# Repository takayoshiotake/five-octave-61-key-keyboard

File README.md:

# Five Octave

[![CC BY-SA 4.0][cc-by-sa-shield]][cc-by-sa]

A 61-key (5-octave) keyboard. Powered by [Vial](https://get.vial.today/) firmware.

## Layout

**Layer 0**:

📄 [keyboard-layout.png](layout/keyboard-layout.png) (v0.3.0)

MEMO: When pressed individually and released, it becomes the lower right keys (英数 and かな).

**Layer 1**:

📄 [keyboard-layout-1.png](layout/keyboard-layout-1.png)

**Layer 2**:

📄 [keyboard-layout-2.png](layout/keyboard-layout-2.png)

MEMO: I couldn't figure out how to achieve 'fn' with adafruit_hid, so I'm using Karabiner to remap right_option to 'fn' and using it that way.

**RAW data for Keyboard Layout Editor v0.15:**

📄 [keyboard-layout.rawdata.json](layout/keyboard-layout.rawdata.json)

```json
[{"a":4,"f":3},"Esc","!\n1","@\n2","#\n3","$\n4","%\n5","^\n6","&\n7","*\n8","(\n9",")\n0","_\n-","+\n=","|\n\\","~\n`"],
[{"w":1.5},"Tab","Q","W","E","R","T","Y","U","I","O","P","{\n[","}\n]",{"w":1.5},"BS"],
[{"w":1.75},"MO(1)\n\n\n英数","A","S","D","F","G","H","J","K","L",":\n;","\"\n'",{"w":2.25},"Return"],
[{"w":2.25},"Shift","Z","X","C","V","B","N","M","<\n,",">\n.","?\n/",{"w":1.75},"Shift","MO(2)"],
[{"w":1.25},"Ctrl",{"w":1.25},"Opt",{"w":1.25},"Cmd\n\n\n英数",{"a":7,"w":6.25},"6.25u",{"a":4},"Cmd\n\n\nかな","Opt"]
```

📄 [keyboard-layout-1.rawdata.json](layout/keyboard-layout-1.rawdata.json)

```json
[{"a":4,"f":3},"Esc",{"c":"#aaccaa"},"F1","F2","F3","F4","F5","F6","F7","F8","F9","F10","F11","F12",{"c":"#cccccc"},"|\n\\","~\n`"],
[{"w":1.5},"Tab",{"c":"#aaccaa"},"Home","Up","End","PgUp",{"c":"#cccccc"},"T","Y","BS",{"c":"#cccccc"},"I","O","P","{\n[","}\n]",{"w":1.5},"BS"],
[{"c":"#aaccaa","w":1.75},"","Left","Down","Right","PgDn",{"c":"#cccccc"},"G",{"c":"#aaccaa"},"Enter","kana",{"c":"#cccccc"},"K","L",":\n;","\"\n'",{"w":2.25},"Return"],
[{"w":2.25},"Shift","Z","X","C","V","B","N","M","<\n,",">\n.","?\n/",{"w":1.75},"Shift",{"c":"#aaccaa"},"",{"c":"#cccccc"}],
[{"w":1.25},"Ctrl",{"w":1.25},"Opt",{"w":1.25},"Cmd\n\n\n英数",{"a":7,"w":6.25},"6.25u",{"a":4},"Cmd\n\n\nかな","Opt"]
```

📄 [keyboard-layout-2.rawdata.json](layout/keyboard-layout-2.rawdata.json)

```json
[{"a":4,"f":3},"Esc",{"c":"#aaccaa"},"F1","F2","F3","F4","F5","F6","F7","F8","F9","F10","F11","F12",{"c":"#cccccc"},"|\n\\","~\n`"],
[{"w":1.5},"Tab","Q","W","E","R","T","Y","U","I","O","P",{"c":"#aaccaa"},"Up",{"c":"#cccccc"},"}\n]",{"w":1.5},"BS"],
[{"c":"#aaccaa","w":1.75},"CapsLock",{"c":"#cccccc"},"A","S","D","F","G","H","J","K","L",{"c":"#aaccaa"},"left","right",{"c":"#cccccc","w":2.25},"Return"],
[{"w":2.25},"Shift","Z","X","C","V","B","N","M","<\n,",">\n.",{"c":"#aaccaa"},"Down",{"c":"#cccccc","w":1.75},"Shift",{"c":"#aaccaa"},"",{"c":"#cccccc"}],
[{"w":1.25},"Ctrl",{"w":1.25},"Opt",{"w":1.25},"Cmd\n\n\n英数",{"a":7,"w":6.25},"6.25u",{"a":4},"Cmd\n\n\nかな","Opt"]]
```

- 🔗 [Keyboard Layout Editor](http://www.keyboard-layout-editor.com/)

## BOM

| Material | QTY | Note |
|-|-:|-|
| Five Octave MCU Board | 1 | |
| Five Octave Keys Board | 1 | |
| Five Octave Enclosure | 1 | |
| 0151660169 | 1 | Molex 0.50mm pitch FFC, Type A, 127.00mm, 16 circuits |

- 🔗 [Molex Connector Part Number - 15166-0169 | Molex](https://www.molex.com/en-us/products/part-detail/151660169)

### Five Octave MCU Board

| Material | Symbol | QTY | Note | JLCPCB Part # |
|-|-|-:|-|-|
| 30pF 0402 | C1, C2 | 2 | | [C1570](https://jlcpcb.com/partdetail/1922-0402CG300J500NT/C1570) |
| 1uF 0402 | C3, C4 | 2 | | [C52923](https://jlcpcb.com/partdetail/53938-CL05A105KA5NQNC/C52923) |
| 100nF 0402 | C5-C14 | 10 | | [C307331](https://jlcpcb.com/partdetail/291005-CL05B104KB54PNC/C307331) |
| 10uF 0402 | C15, C16 | 2 | | [C15525](https://jlcpcb.com/partdetail/16204-CL05A106MQ5NUNC/C15525) |
| HRO_TYPE-C-31-M-12 | J1 | 1 | USB Type-C Connector, Korean Hroparts Elec | [C165948](https://jlcpcb.com/partdetail/Korean_HropartsElec-TYPE_C_31_M12/C165948) |
| AFC01-S16FCC-00 | J2 | 1 | FFC Connector 0.50mm pitch 16 circuits, JUSHUO | [C262272](https://jlcpcb.com/partdetail/Jushuo-AFC01_S16FCC00/C262272) |
| WS2812C-2020-V1 | LED1 | 1 | NeoPixel RGB LED 2x2mm, Worldsemi | [C2976072](https://jlcpcb.com/partdetail/Worldsemi-WS2812C_2020V1/C2976072) |
| 10KΩ 0402 | R1, R3 | 2 | | [C25744](https://jlcpcb.com/partdetail/26487-0402WGF1002TCE/C25744) |
| 1KΩ 0402 | R2, R4 | 2 | | [C11702](https://jlcpcb.com/partdetail/12256-0402WGF1001TCE/C11702) |
| 27Ω 0402 | R5, R6 | 2 | | [C352446](https://jlcpcb.com/partdetail/Resi-AECR0402F27R0K9/C352446) |
| 5.1KΩ 0402 | R7, R8 | 2 | | [C25905](https://jlcpcb.com/partdetail/26648-0402WGF5101TCE/C25905) |
| SKRPANE010 | SW1, SW2 | 2 | Tactile Switch, ALPS ALPINE | [C470426](https://jlcpcb.com/partdetail/Alpsalpine-SKRPANE010/C470426) |
| RP2040 | U1 | 1 | MCU, Raspberry Pi | [C2040](https://jlcpcb.com/partdetail/RaspberryPi-RP2040/C2040) |
| W25Q64JVXGIQ | U2 | 1 | 64M-bit Serial Flash, Winbond Electronics | [C2940195](https://jlcpcb.com/partdetail/WinbondElec-W25Q64JVXGIQ/C2940195) |
| AP2112K-3.3TRG1 | U3 | 1 | 3.3V Linear Voltage Regulators | [C51118](https://jlcpcb.com/partdetail/DiodesIncorporated-AP2112K_33TRG1/C51118) |
| X322512MSB4SI | Y1 | 1 | 12MHz 20pF Crystal Resonator, SMD-3225, Yangxing Tech | [C9002](https://jlcpcb.com/partdetail/YangxingTech-X322512MSB4SI/C9002) | 

### Five Octave Keys Board

| Material | Symbol | QTY | Note | JLCPCB Part # |
|-|-|-:|-|-|
| 1N4148WS | D1-D61 | 61 | | [C2128](https://jlcpcb.com/partdetail/2485-1N4148WS/C2128) |
| CPG151101S11-16 | SW1-SW61 | 61 | How Swap Socket, Kailh | [C5156480](https://jlcpcb.com/partdetail/Kailh-CPG151101S1116/C5156480) | 
| AFC01-S16FCC-00 | J1 | 1 | FFC Connector 0.50mm pitch 16 circuits, JUSHUO | [C262272](https://jlcpcb.com/partdetail/Jushuo-AFC01_S16FCC00/C262272) |

- 🔗 [JLCPCB | Assembly Parts Lib](https://jlcpcb.com/parts)

### Five Octave Enclosure

| Material | Symbol | QTY | Note |
|-|-|-:|-|
| Five Octave Enclosure - Case || 1 | (or Enclosure v2) |
| Five Octave Enclosure - Top Frame || 1 | (or Enclosure v2) |
| Screw M2 x 8mm || 4 | Secure Case and Top Frame |
| Screw M2 x 5mm or 4mm || 4 | Secure Case and Five Octave MCU |
| Poron 1.5t 3mm x 120mm || 2 | For gasket mounting |
| Poron 1.5t 3mm x 60mm || 6 | For gasket mounting |
| Poron 1.5t 3mm x 40mm || 2 | For gasket mounting |

## Schematic and PCB

### Five Octave MCU

📄 [Five_Octave_MCU.kicad_sch](electronics/Five_Octave_MCU/Five_Octave_MCU.kicad_sch) (v1.0.0)

📄 [Five_Octave_MCU.kicad_pcb](electronics/Five_Octave_MCU/Five_Octave_MCU.kicad_pcb) (v1.0.0)

📄 [Five_Octave_MCU.svg](electronics/Five_Octave_MCU/Five_Octave_MCU.svg)

### Five Octave Keys

📄 [Five_Octave_Keys.kicad_sch](electronics/Five_Octave_Keys/Five_Octave_Keys.kicad_sch) (v1.0.0)

📄 [Five_Octave_Keys.kicad_pcb](electronics/Five_Octave_Keys/Five_Octave_Keys.kicad_pcb) (v1.0.0)

📄 [Five_Octave_Keys.svg](electronics/Five_Octave_Keys/Five_Octave_Keys.svg)

#### Key-matrix (8x8)

|    | C0    | C1   | C2  | C3  | C4    | C5    | C6     | C7    |
|----|-------|------|-----|-----|-------|-------|--------|-------|
| R0 | Esc   |      | 1   | 2   | 3     | 4     | 5      | 6     |
| R1 | Tab   |      |     | Q   | W     | E     | R      | T     |
| R2 | Caps  | Z    | X   | A   | S     | D     | F      | G     | 
| R3 | Shift | Ctrl | Opt | Cmd | Space | C     | V      | B     |
| R4 | 7     | 8    | 9   | 0   | -     | =     | \      | `     |
| R5 | Y     | U    | I   | O   | P     | [     | ]      | BS    |
| R6 | H     | J    | K   | L   | ;     | '     | Return | Fn    |
| R7 | N     | M    | ,   | .   | /     | Shift | Cmd    | MO(1) | 

## Mechanics

### Five Octave Enclosure

📄 [Five_Octave_Enclosure.FCStd](mechanics/Five_Octave_Enclosure.FCStd) (v1.0.1)

### Five Octave Enclosure v2

📄 [Five_Octave_Enclosure_v2.FCStd](mechanics/Five_Octave_Enclosure_v2.FCStd) (v2.1.2)

### Plate

📄 [Five_Octave_Plate.kicad_pcb](electronics/Five_Octave_Plate/Five_Octave_Plate.kicad_pcb) (v1.0.0)

## Firmware

You can use Vial or CircuitPython.

### Vial

- Built UF2
    - 📄 [takayoshiotake_five_octave_vial_20240103.uf2](vial-bin/takayoshiotake_five_octave_vial_20240103.uf2)
- Code
    -  🔗 <https://github.com/vial-kb/vial-qmk/tree/vial/keyboards/takayoshiotake/five_octave>
    -  🔗 <https://github.com/vial-kb/vial-qmk/tree/49f5eec0d46f3524850885ffae9dee2982312e50>

See [vial-porting](vial-porting) for more details.

### CircuitPython

Software for the Five Octave runs on CircuitPython.
Its CircuitPython is the same as the one for Octave (<https://github.com/takayoshiotake/octave-12-key-macropad>).

- Built UF2
    - 🔗 <https://adafruit-circuit-python.s3.amazonaws.com/index.html?prefix=bin/takayoshiotake_octave_rp2040/>
    - 📄 [adafruit-circuitpython-takayoshiotake_octave_rp2040-en_US-8.2.6.uf2](circuitpython-bin/adafruit-circuitpython-takayoshiotake_octave_rp2040-en_US-8.2.6.uf2)
- Code
    - 🔗 [adafruit/circuitpython](https://github.com/adafruit/circuitpython)
        - 🔗 <https://github.com/adafruit/circuitpython/tree/main/ports/raspberrypi/boards/takayoshiotake_octave_rp2040>

See [circuitpython-app/README.md](software/README.md) for application software.

## Gallery

Keycap: Drop + biip MT3 Extended 2048

MEMO: Alminum 6061 CNC + Bead blasting 120 mesh + Anodizing natural matte by JLCPCB (Five Octave Enclosure v1.0.0)

### Photos with Enclosure v2

Keycap: Drop + biip MT3 Extended 2048

MEMO: Alminum 6061 CNC + Bead blasting 150 mesh + Hardcoat anodizing natural matte by JLCPCB (Five Octave Enclosure v2.1.1)

## License

This work is licensed under a
[Creative Commons Attribution-ShareAlike 4.0 International License][cc-by-sa].

[![CC BY-SA 4.0][cc-by-sa-image]][cc-by-sa]

[cc-by-sa]: http://creativecommons.org/licenses/by-sa/4.0/
[cc-by-sa-image]: https://licensebuttons.net/l/by-sa/4.0/88x31.png
[cc-by-sa-shield]: https://img.shields.io/badge/license-CC%20BY--SA%204.0-lightgrey.svg

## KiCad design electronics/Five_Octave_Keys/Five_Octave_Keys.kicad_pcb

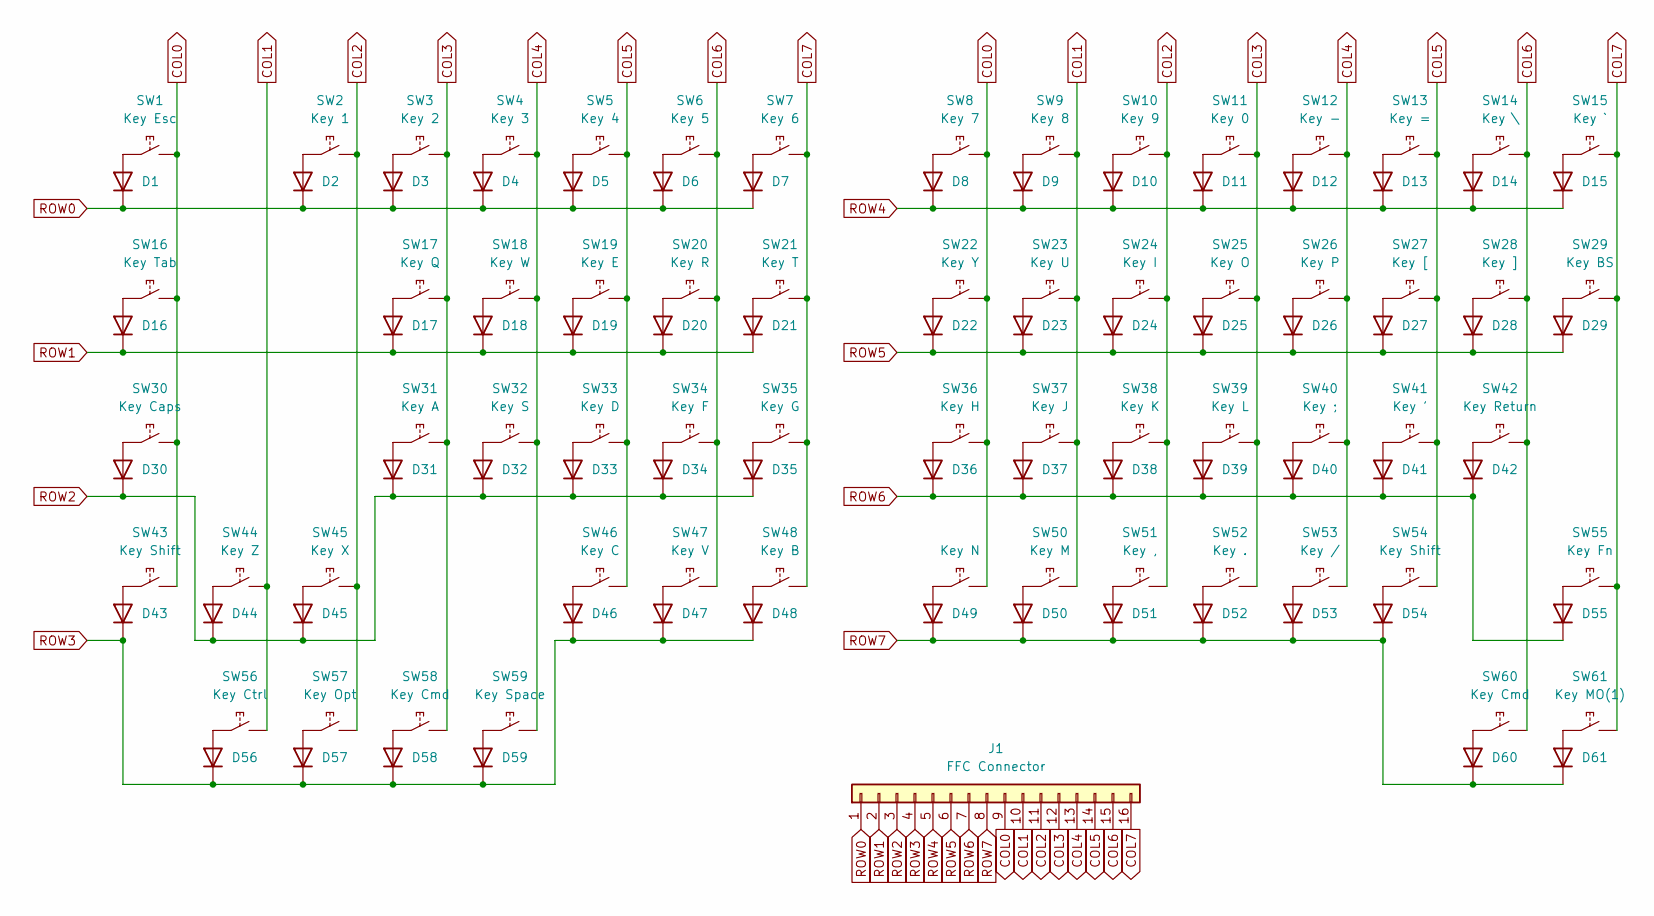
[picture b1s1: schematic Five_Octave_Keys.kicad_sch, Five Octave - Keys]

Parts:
D1, D2, D3, D4, D5, D6, D7, D8, D9, D10, D11, D12, D13, D14, D15, D16, D17, D18, D19, D20, D21, D22, D23, D24, D25, D26, D27, D28, D29, D30, D31, D32, D33, D34, D35, D36, D37, D38, D39, D40, D41, D42, D43, D44, D45, D46, D47, D48, D49, D50, D51, D52, D53, D54, D55, D56, D57, D58, D59, D60, D61: 1N4148WS; D_SOD-323F; LCSC C2128
J1: FFC Connector; JUSHUO_AFC01-S16FCC-00; LCSC C262272
SW1: Key Esc; Hot_Swap_Socket_CPG151101S11; LCSC C5156480
SW2: Key 1; Hot_Swap_Socket_CPG151101S11; LCSC C5156480
SW3: Key 2; Hot_Swap_Socket_CPG151101S11; LCSC C5156480
SW4: Key 3; Hot_Swap_Socket_CPG151101S11; LCSC C5156480
SW5: Key 4; Hot_Swap_Socket_CPG151101S11; LCSC C5156480
SW6: Key 5; Hot_Swap_Socket_CPG151101S11; LCSC C5156480
SW7: Key 6; Hot_Swap_Socket_CPG151101S11; LCSC C5156480
SW8: Key 7; Hot_Swap_Socket_CPG151101S11; LCSC C5156480
SW9: Key 8; Hot_Swap_Socket_CPG151101S11; LCSC C5156480
SW10: Key 9; Hot_Swap_Socket_CPG151101S11; LCSC C5156480
SW11: Key 0; Hot_Swap_Socket_CPG151101S11; LCSC C5156480
SW12: Key -; Hot_Swap_Socket_CPG151101S11; LCSC C5156480
SW13: Key =; Hot_Swap_Socket_CPG151101S11; LCSC C5156480
SW14: Key \; Hot_Swap_Socket_CPG151101S11; LCSC C5156480
SW15: Key `; Hot_Swap_Socket_CPG151101S11; LCSC C5156480
SW16: Key Tab; Hot_Swap_Socket_CPG151101S11; LCSC C5156480
SW17: Key Q; Hot_Swap_Socket_CPG151101S11; LCSC C5156480
SW18: Key W; Hot_Swap_Socket_CPG151101S11; LCSC C5156480
SW19: Key E; Hot_Swap_Socket_CPG151101S11; LCSC C5156480
SW20: Key R; Hot_Swap_Socket_CPG151101S11; LCSC C5156480
SW21: Key T; Hot_Swap_Socket_CPG151101S11; LCSC C5156480
SW22: Key Y; Hot_Swap_Socket_CPG151101S11; LCSC C5156480
SW23: Key U; Hot_Swap_Socket_CPG151101S11; LCSC C5156480
SW24: Key I; Hot_Swap_Socket_CPG151101S11; LCSC C5156480
SW25: Key O; Hot_Swap_Socket_CPG151101S11; LCSC C5156480
SW26: Key P; Hot_Swap_Socket_CPG151101S11; LCSC C5156480
SW27: Key [; Hot_Swap_Socket_CPG151101S11; LCSC C5156480
SW28: Key ]; Hot_Swap_Socket_CPG151101S11; LCSC C5156480
SW29: Key BS; Hot_Swap_Socket_CPG151101S11; LCSC C5156480
SW30: Key Caps; Hot_Swap_Socket_CPG151101S11; LCSC C5156480
SW31: Key A; Hot_Swap_Socket_CPG151101S11; LCSC C5156480
SW32: Key S; Hot_Swap_Socket_CPG151101S11; LCSC C5156480
SW33: Key D; Hot_Swap_Socket_CPG151101S11; LCSC C5156480
SW34: Key F; Hot_Swap_Socket_CPG151101S11; LCSC C5156480
SW35: Key G; Hot_Swap_Socket_CPG151101S11; LCSC C5156480
SW36: Key H; Hot_Swap_Socket_CPG151101S11; LCSC C5156480
SW37: Key J; Hot_Swap_Socket_CPG151101S11; LCSC C5156480
SW38: Key K; Hot_Swap_Socket_CPG151101S11; LCSC C5156480
SW39: Key L; Hot_Swap_Socket_CPG151101S11; LCSC C5156480
SW40: Key ;; Hot_Swap_Socket_CPG151101S11; LCSC C5156480
SW41: Key '; Hot_Swap_Socket_CPG151101S11; LCSC C5156480
SW42: Key Return; Hot_Swap_Socket_CPG151101S11; LCSC C5156480
SW43, SW54: Key Shift; Hot_Swap_Socket_CPG151101S11; LCSC C5156480
SW44: Key Z; Hot_Swap_Socket_CPG151101S11; LCSC C5156480
SW45: Key X; Hot_Swap_Socket_CPG151101S11; LCSC C5156480
SW46: Key C; Hot_Swap_Socket_CPG151101S11; LCSC C5156480
SW47: Key V; Hot_Swap_Socket_CPG151101S11; LCSC C5156480
SW48: Key B; Hot_Swap_Socket_CPG151101S11; LCSC C5156480
SW49: Key N; Hot_Swap_Socket_CPG151101S11; LCSC C5156480
SW50: Key M; Hot_Swap_Socket_CPG151101S11; LCSC C5156480
SW51: Key ,; Hot_Swap_Socket_CPG151101S11; LCSC C5156480
SW52: Key .; Hot_Swap_Socket_CPG151101S11; LCSC C5156480
SW53: Key /; Hot_Swap_Socket_CPG151101S11; LCSC C5156480
SW55: Key Fn; Hot_Swap_Socket_CPG151101S11; LCSC C5156480
SW56: Key Ctrl; Hot_Swap_Socket_CPG151101S11; LCSC C5156480
SW57: Key Opt; Hot_Swap_Socket_CPG151101S11; LCSC C5156480
SW58, SW60: Key Cmd; Hot_Swap_Socket_CPG151101S11; LCSC C5156480
SW59: Key Space; Hot_Swap_Socket_CPG151101S11; LCSC C5156480
SW61: Key MO(1); Hot_Swap_Socket_CPG151101S11; LCSC C5156480

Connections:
COL0: J1.9, SW1.2, SW8.2, SW16.2, SW22.2, SW30.2, SW36.2, SW43.2, SW49.2
COL1: J1.10, SW9.2, SW23.2, SW37.2, SW44.2, SW50.2, SW56.2
COL2: J1.11, SW2.2, SW10.2, SW24.2, SW38.2, SW45.2, SW51.2, SW57.2
COL3: J1.12, SW3.2, SW11.2, SW17.2, SW25.2, SW31.2, SW39.2, SW52.2, SW58.2
COL4: J1.13, SW4.2, SW12.2, SW18.2, SW26.2, SW32.2, SW40.2, SW53.2, SW59.2
COL5: J1.14, SW5.2, SW13.2, SW19.2, SW27.2, SW33.2, SW41.2, SW46.2, SW54.2
COL6: J1.15, SW6.2, SW14.2, SW20.2, SW28.2, SW34.2, SW42.2, SW47.2, SW60.2
COL7: J1.16, SW7.2, SW15.2, SW21.2, SW29.2, SW35.2, SW48.2, SW55.2, SW61.2
unnamed: D1.2 (A), SW1.1
unnamed: D2.2 (A), SW2.1
unnamed: D3.2 (A), SW3.1
unnamed: D4.2 (A), SW4.1
unnamed: D5.2 (A), SW5.1
unnamed: D6.2 (A), SW6.1
unnamed: D7.2 (A), SW7.1
unnamed: D8.2 (A), SW8.1
unnamed: D9.2 (A), SW9.1
unnamed: D10.2 (A), SW10.1
unnamed: D11.2 (A), SW11.1
unnamed: D12.2 (A), SW12.1
unnamed: D13.2 (A), SW13.1
unnamed: D14.2 (A), SW14.1
unnamed: D15.2 (A), SW15.1
unnamed: D16.2 (A), SW16.1
unnamed: D17.2 (A), SW17.1
unnamed: D18.2 (A), SW18.1
unnamed: D19.2 (A), SW19.1
unnamed: D20.2 (A), SW20.1
unnamed: D21.2 (A), SW21.1
unnamed: D22.2 (A), SW22.1
unnamed: D23.2 (A), SW23.1
unnamed: D24.2 (A), SW24.1
unnamed: D25.2 (A), SW25.1
unnamed: D26.2 (A), SW26.1
unnamed: D27.2 (A), SW27.1
unnamed: D28.2 (A), SW28.1
unnamed: D29.2 (A), SW29.1
unnamed: D30.2 (A), SW30.1
unnamed: D31.2 (A), SW31.1
unnamed: D32.2 (A), SW32.1
unnamed: D33.2 (A), SW33.1
unnamed: D34.2 (A), SW34.1
unnamed: D35.2 (A), SW35.1
unnamed: D36.2 (A), SW36.1
unnamed: D37.2 (A), SW37.1
unnamed: D38.2 (A), SW38.1
unnamed: D39.2 (A), SW39.1
unnamed: D40.2 (A), SW40.1
unnamed: D41.2 (A), SW41.1
unnamed: D42.2 (A), SW42.1
unnamed: D43.2 (A), SW43.1
unnamed: D44.2 (A), SW44.1
unnamed: D45.2 (A), SW45.1
unnamed: D46.2 (A), SW46.1
unnamed: D47.2 (A), SW47.1
unnamed: D48.2 (A), SW48.1
unnamed: D49.2 (A), SW49.1
unnamed: D50.2 (A), SW50.1
unnamed: D51.2 (A), SW51.1
unnamed: D52.2 (A), SW52.1
unnamed: D53.2 (A), SW53.1
unnamed: D54.2 (A), SW54.1
unnamed: D55.2 (A), SW55.1
unnamed: D56.2 (A), SW56.1
unnamed: D57.2 (A), SW57.1
unnamed: D58.2 (A), SW58.1
unnamed: D59.2 (A), SW59.1
unnamed: D60.2 (A), SW60.1
unnamed: D61.2 (A), SW61.1
ROW0: D1.1 (K), D2.1 (K), D3.1 (K), D4.1 (K), D5.1 (K), D6.1 (K), D7.1 (K), J1.1
ROW1: D16.1 (K), D17.1 (K), D18.1 (K), D19.1 (K), D20.1 (K), D21.1 (K), J1.2
ROW2: D30.1 (K), D31.1 (K), D32.1 (K), D33.1 (K), D34.1 (K), D35.1 (K), D44.1 (K), D45.1 (K), J1.3
ROW3: D43.1 (K), D46.1 (K), D47.1 (K), D48.1 (K), D56.1 (K), D57.1 (K), D58.1 (K), D59.1 (K), J1.4
ROW4: D8.1 (K), D9.1 (K), D10.1 (K), D11.1 (K), D12.1 (K), D13.1 (K), D14.1 (K), D15.1 (K), J1.5
ROW5: D22.1 (K), D23.1 (K), D24.1 (K), D25.1 (K), D26.1 (K), D27.1 (K), D28.1 (K), D29.1 (K), J1.6
ROW6: D36.1 (K), D37.1 (K), D38.1 (K), D39.1 (K), D40.1 (K), D41.1 (K), D42.1 (K), D55.1 (K), J1.7
ROW7: D49.1 (K), D50.1 (K), D51.1 (K), D52.1 (K), D53.1 (K), D54.1 (K), D60.1 (K), D61.1 (K), J1.8

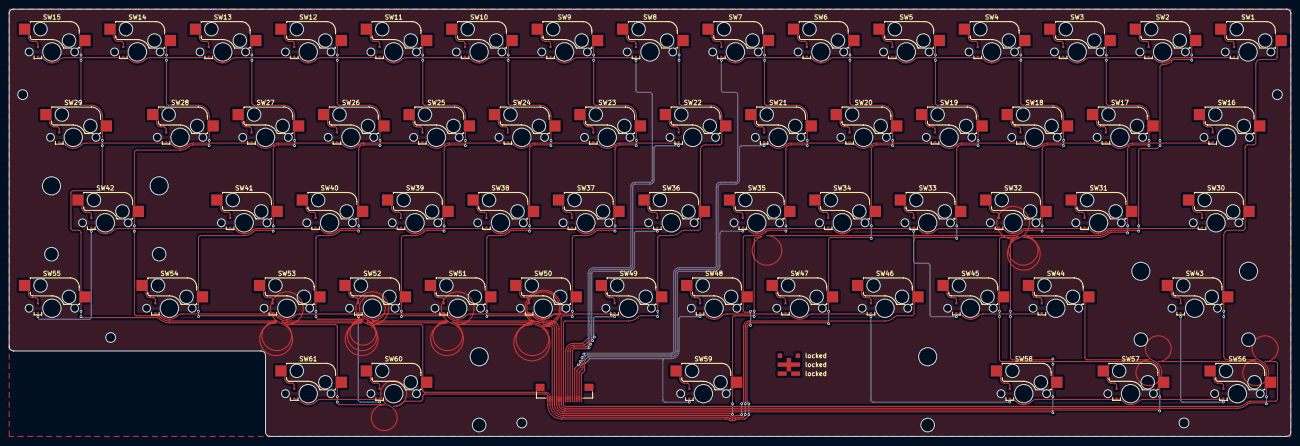
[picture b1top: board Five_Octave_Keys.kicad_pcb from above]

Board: 2 copper layers, 285.7 x 95.2 mm, 123 parts (0 on the bottom side), 77 nets.

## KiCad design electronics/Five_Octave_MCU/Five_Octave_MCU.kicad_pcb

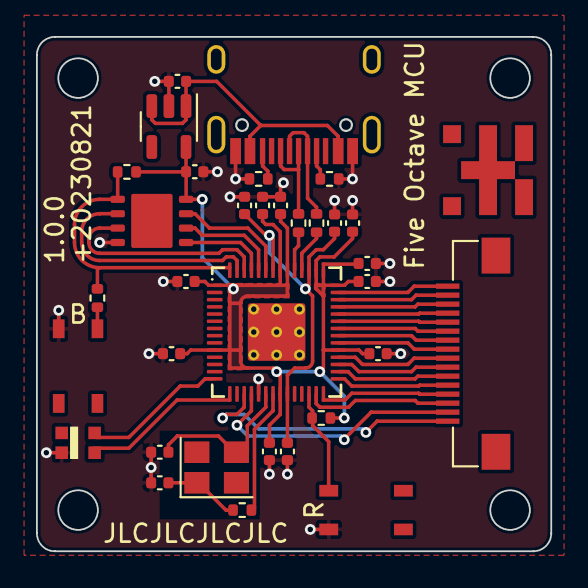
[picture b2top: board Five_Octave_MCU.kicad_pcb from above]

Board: 2 copper layers, 28.6 x 28.6 mm, 33 parts (0 on the bottom side), 39 nets.

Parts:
C1, C2: 30pF; C_0402_1005Metric
C3, C4: 1uF; C_0402_1005Metric
C5, C6, C7, C8, C9, C10, C11, C12, C13, C14: 0.1uF; C_0402_1005Metric
C15, C16: 10uF; C_0402_1005Metric
J1: HRO_TYPE-C-31-M-12
J2: FFC Connector; JUSHUO_AFC01-S16FCC-00
LED1: WS2812C-2020-V1; WS2812C-2020
R1, R3: 10K; R_0402_1005Metric
R2, R4: 1K; R_0402_1005Metric
R5, R6: 27; R_0402_1005Metric
R7, R8: 5.1K; R_0402_1005Metric
SW1, SW2: Alps_Alpine_SKRP; Tactile_Switch_SKRP_Series
U1: Raspberry_Pi_RP2040; RP2040_QFN-56
U2: W25Q64JVXGIQ; XSON-8-EP_4x4mm
U3: AP2112K-3.3; SOT-23-5
Y1: 12MHz; Crystal_SMD_3225-4Pin_3.2x2.5mm

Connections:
+1V1: C4.1, C13.1, C14.1, U1.23 (DVDD), U1.45 (VREG_VOUT), U1.50 (DVDD)
+3V3: C3.1, C5.1, C6.1, C7.1, C8.1, C9.1, C10.1, C11.1, C12.1, C16.1, R1.1, R3.1, U1.1 (IOVDD), U1.10 (IOVDD), U1.22 (IOVDD), U1.33 (IOVDD), U1.42 (IOVDD), U1.43 (ADC_AVDD), U1.44 (VREG_VIN), U1.48 (USB_VDD), U1.49 (IOVDD), U2.8 (VCC), U3.5 (VOUT)
+5V: C15.1, J1.A4/B9 (VBUS), J1.A9/B4 (VBUS), U3.1 (VIN), U3.3 (EN)
COL0: J2.8, U1.32 (GPIO21)
COL1: J2.7, U1.31 (GPIO20)
COL2: J2.6, U1.30 (GPIO19)
COL3: J2.5, U1.29 (GPIO18)
COL4: J2.4, U1.28 (GPIO17)
COL5: J2.3, U1.27 (GPIO16)
COL6: J2.2, U1.18 (GPIO15)
COL7: J2.1, U1.17 (GPIO14)
D+: R5.1, U1.47 (USB_DP)
D-: R6.1, U1.46 (USB_DM)
GND: C1.2, C2.2, C3.2, C4.2, C5.2, C6.2, C7.2, C8.2, C9.2, C10.2, C11.2, C12.2, C13.2, C14.2, C15.2, C16.2, J1.A1/B12 (GND), J1.A12/B1 (GND), LED1.3 (VSS), R7.2, R8.2, SW1.3, SW2.3, U1.19 (TESTEN), U1.57 (GND), U2.4 (GND), U3.2 (GND)
NEOPIX: LED1.4 (DIN), U1.15 (GPIO12)
NEOPIX_POWER: LED1.1 (VDD), U1.14 (GPIO11)
unnamed: C2.1, R2.2, Y1.1
unnamed: J1.A5 (CC1), R8.1
unnamed: J1.B5 (CC2), R7.1
unnamed: J1.A6 (D+), J1.B6 (D+), R5.2
unnamed: J1.A7 (D-), J1.B7 (D-), R6.2
unnamed: R4.2, SW2.1
unnamed: U1.52 (QSPI_SCLK), U2.6 (CLK)
unnamed: U1.53 (QSPI_SD0), U2.5 (DI(IO0))
unnamed: U1.55 (QSPI_SD1), U2.2 (DO(IO1))
unnamed: U1.54 (QSPI_SD2), U2.3 (IO2)
unnamed: U1.51 (QSPI_SD3), U2.7 (IO3)
unnamed: R1.2, SW1.1, U1.26 (RUN)
unnamed: C1.1, U1.20 (XIN), Y1.3
unnamed: R2.1, U1.21 (XOUT)
QSPI_SS_N: R3.2, R4.1, U1.56 (QSPI_SS_N), U2.1 (~CS)
ROW0: J2.16, U1.41 (GPIO29/ADC3)
ROW1: J2.15, U1.40 (GPIO28/ADC2)
ROW2: J2.14, U1.39 (GPIO27/ADC1)
ROW3: J2.13, U1.38 (GPIO26/ADC0)
ROW4: J2.12, U1.37 (GPIO25)
ROW5: J2.11, U1.36 (GPIO24)
ROW6: J2.10, U1.35 (GPIO23)
ROW7: J2.9, U1.34 (GPIO22)

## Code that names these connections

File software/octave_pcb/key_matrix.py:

import time

import board
import digitalio

DIGITALIO_HIGH = True
DIGITALIO_LOW = False


class KeyMatrix:
  def __init__(self):
    row_pins = [board.GPIO29, board.GPIO28, board.GPIO27, board.GPIO26,
                board.GPIO25, board.GPIO24, board.GPIO23, board.GPIO22]
    self.row_ios = [digitalio.DigitalInOut(pin) for pin in row_pins]
    for row_io in self.row_ios:
      row_io.switch_to_output(DIGITALIO_HIGH, digitalio.DriveMode.OPEN_DRAIN)

    col_pins = [board.GPIO21, board.GPIO20, board.GPIO19, board.GPIO18,
                board.GPIO17, board.GPIO16, board.GPIO15, board.GPIO14]
    self.col_ios = [digitalio.DigitalInOut(pin) for pin in col_pins]
    for col_io in self.col_ios:
      col_io.switch_to_input(digitalio.Pull.UP)

  def deinit(self):
    self.select_row(-1)
    for row_io in self.row_ios:
      row_io.deinit()
    for col_io in self.col_ios:
      col_io.deinit()

  def select_row(self, row):
    # Once deselect all rows
    for row_io in self.row_ios:
      row_io.value = DIGITALIO_HIGH
    if 0 <= row <= len(self.row_ios):
      self.row_ios[row].value = DIGITALIO_LOW

  def scan_matrix(self):
    are_keys_pressed = []
    for row in range(len(self.row_ios)):
      self.select_row(row)
      are_keys_pressed.extend(
          [True if col_io.value == DIGITALIO_LOW else False for col_io in self.col_ios]
      )
      # time.sleep(0.001)
    return are_keys_pressed

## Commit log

2023-07-06 Add README
2023-07-06 Fix format of keyboard-layout.rawdata.json
2023-07-08 Add KiCad project and project library
2023-07-08 Fix library path
2023-07-08 Add 8x8 key matrix schematic
2023-07-09 Modify footprint of hot-swap socket
2023-07-09 Add footprint of stabilizer (2u)
2023-07-15 Adjust footprint of stabilizer (2u)
2023-07-15 Add footprint of stabilizer (6.25u)
2023-07-15 Test footprint of stabilizer
2023-07-27 Adjust stabilizer holes
2023-07-29 Assign C2128 to the LCSC value of 1N4148WS
2023-07-29 Add connector footprint
2023-07-29 Add FFC connector
2023-07-29 Layout Keys board
2023-07-30 Wire diodes to switches
2023-07-31 Route some diodes
2023-08-01 Adjust key-matrix
2023-08-05 Update pcb
2023-08-09 Adjust footprint of FCC connector
2023-08-09 Add 3d shape for FCC connector
2023-08-10 Update
    - Assign JLCPCB part number to SW1-61
    - GH60 compatible
2023-08-10 Decorate PCB with silkscreen
2023-08-12 Fix footprint orientation for PCBA
2023-08-12 Remove screw holes
2023-08-12 Start MCU board design
2023-08-14 Assign LCSC values
2023-08-14 Round off insignificant decimals
2023-08-14 Update footprint
2023-08-14 Change zone pad connections to thermal reliefs
2023-08-14 Update footprint for FFC connector
2023-08-14 Change M2 footprint
2023-08-15 Fix FFC connector assignment
2023-08-15 Add plate design
2023-08-15 Improve edge-cuts layer
2023-08-15 Fix Shift and Fn key size
2023-08-15 Modify outline curve
2023-08-20 Add enclosure design (WIP)
2023-08-21 Change footprint for AP2112K-3.3
2023-08-21 Update build number
2023-08-21 Update version
2023-08-22 Add PCBA ver of Keys PCB
2023-08-24 Improve enclosure
2023-08-26 Update enclosure
    Add weight-bar
2023-08-28 Add decorative dimple to an enclosure
2023-08-29 Update enclosure
2023-08-30 Fix FFC cable type
2023-09-11 Update inner R of enclosure for CNC
2023-09-28 Add hello software
2023-09-28 Add Esc key press event
2023-09-28 Change to boot without mounting
2023-09-30 Support Layer0 key events
2023-09-30 Change the key-map to be more clear
2023-09-30 Add software readme
2023-10-01 Add ComplexModifier
2023-10-01 Change MO1
2023-10-01 Add TechDraw of Case
2023-10-18 Add extension recommendations for vscode
2023-10-22 Fix top frame inner radius, expand the space with the key switch
2023-10-22 Add overview photo
2023-10-22 Add BOM of enclosure
2023-10-22 Add HHKB-like cursor keys
2023-10-22 Change scan rate
2023-10-22 Modify key layers
2023-10-30 Change Layer 2 key-mapping
2023-10-30 Update key-mapping, and add images of each layer keys
2023-10-31 Modify top frame design
    - Extend the margin with the keys.
    - Make the height thinner.
    - Fine-tune the bottom-right dimple.
2023-11-02 Add key code definitions
2023-11-11 Simplify
2023-11-11 Add TechDraw
2023-11-11 Add foot guide
2023-11-18 Update enclosure design
2023-11-19 Improve
2023-11-19 V up enclosure v2
2023-11-21 Remove burr
2023-12-09 Fix MCU screw hole depth of case-v2
2023-12-10 Add keyboard photos
2024-01-03 Add vial firmware
2024-01-10 Update vial-porting codes
2024-03-06 Create LICENSE
